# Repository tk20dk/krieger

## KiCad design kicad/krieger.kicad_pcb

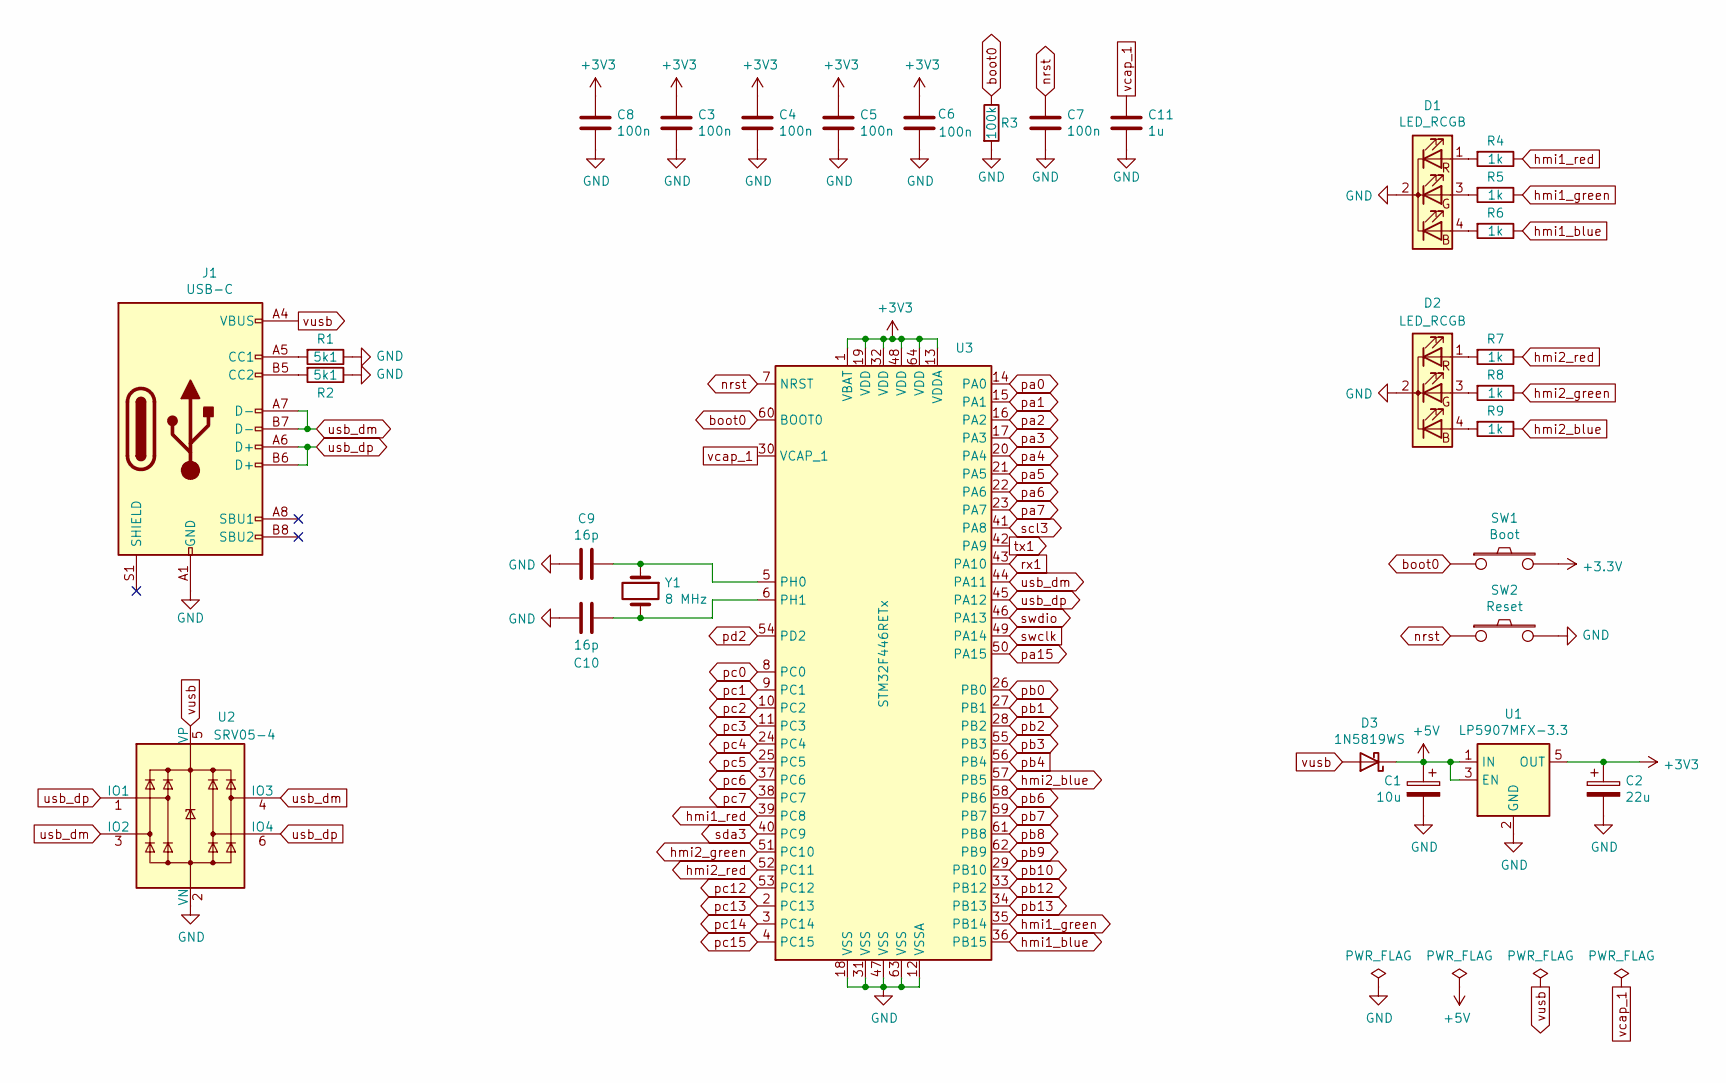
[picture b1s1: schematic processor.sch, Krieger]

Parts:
C1: 10u; CP_EIA-3528-12_Kemet-T
C2: 22u; CP_EIA-3528-12_Kemet-T
C3, C4, C5, C6, C7, C8: 100n; C_0603_1608Metric
C9, C10: 16p; C_0603_1608Metric
C11: 1u; C_0603_1608Metric
D1, D2: LED_RCGB; LED_D5.0mm-4
D3: 1N5819WS; D_SOD-323_HandSoldering
J1: USB-C; USB_C_Receptacle_HRO_TYPE-C-31-M-12
R1, R2: 5k1; R_0603_1608Metric
R3: 100k; R_0603_1608Metric
R4, R5, R6, R7, R8, R9: 1k; R_0603_1608Metric
SW1: Boot; TACT-SWITCH
SW2: Reset; TACT-SWITCH
U1: LP5907MFX-3.3; SOT-23-5
U2: SRV05-4; SOT-23-6
U3: STM32F446RETx; LQFP-64_10x10mm_P0.5mm
Y1: 8 MHz; Crystal_SMD_5032-2Pin_5.0x3.2mm

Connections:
+5V: C1.1, D3.1 (K), U1.1 (IN), U1.3 (EN); also elsewhere on the board
GND: C1.2, C2.2, C3.2, C4.2, C5.2, C6.2, C7.2, C8.2, C9.2, C10.2, C11.2, D1.2 (K), D2.2 (K), J1.A1 (GND), J1.A12 (GND), J1.B1 (GND), J1.B12 (GND), R1.1, R2.1, R3.2, SW2.2, U1.2 (GND), U2.2 (VN), U3.12 (VSSA), U3.18 (VSS), U3.31 (VSS), U3.47 (VSS), U3.63 (VSS); also elsewhere on the board
unnamed: C9.1, U3.5 (PH0), Y1.1
unnamed: C10.1, U3.6 (PH1), Y1.2
unnamed: D1.1 (RA), R4.2
unnamed: D1.3 (GA), R5.2
unnamed: D1.4 (BA), R6.2
unnamed: D2.1 (RA), R7.2
unnamed: D2.3 (GA), R8.2
unnamed: D2.4 (BA), R9.2
unnamed: J1.A5 (CC1), R1.2
unnamed: J1.B5 (CC2), R2.2
boot0: R3.1, SW1.1, U3.60 (BOOT0); also elsewhere on the board
hmi1_blue: R6.1, U3.36 (PB15); also elsewhere on the board
hmi1_green: R5.1, U3.35 (PB14); also elsewhere on the board
hmi1_red: R4.1, U3.39 (PC8); also elsewhere on the board
hmi2_blue: R9.1, U3.57 (PB5); also elsewhere on the board
hmi2_green: R8.1, U3.51 (PC10); also elsewhere on the board
hmi2_red: R7.1, U3.52 (PC11); also elsewhere on the board
nrst: C7.1, SW2.1, U3.7 (NRST); also elsewhere on the board
pa0: U3.14 (PA0); also elsewhere on the board
pa1: U3.15 (PA1); also elsewhere on the board
pa2: U3.16 (PA2); also elsewhere on the board
pa3: U3.17 (PA3); also elsewhere on the board
pa4: U3.20 (PA4); also elsewhere on the board
pa5: U3.21 (PA5); also elsewhere on the board
pa6: U3.22 (PA6); also elsewhere on the board
pa7: U3.23 (PA7); also elsewhere on the board
pa15: U3.50 (PA15); also elsewhere on the board
pb0: U3.26 (PB0); also elsewhere on the board
pb1: U3.27 (PB1); also elsewhere on the board
pb2: U3.28 (PB2); also elsewhere on the board
pb3: U3.55 (PB3); also elsewhere on the board
pb4: U3.56 (PB4); also elsewhere on the board
pb6: U3.58 (PB6); also elsewhere on the board
pb7: U3.59 (PB7); also elsewhere on the board
pb8: U3.61 (PB8); also elsewhere on the board
pb9: U3.62 (PB9); also elsewhere on the board
pb10: U3.29 (PB10); also elsewhere on the board
pb12: U3.33 (PB12); also elsewhere on the board
pb13: U3.34 (PB13); also elsewhere on the board
pc0: U3.8 (PC0); also elsewhere on the board
pc1: U3.9 (PC1); also elsewhere on the board
pc2: U3.10 (PC2); also elsewhere on the board
pc3: U3.11 (PC3); also elsewhere on the board
pc4: U3.24 (PC4); also elsewhere on the board
pc5: U3.25 (PC5); also elsewhere on the board
pc6: U3.37 (PC6); also elsewhere on the board
pc7: U3.38 (PC7); also elsewhere on the board
pc12: U3.53 (PC12); also elsewhere on the board
pc13: U3.2 (PC13); also elsewhere on the board
pc14: U3.3 (PC14); also elsewhere on the board
pc15: U3.4 (PC15); also elsewhere on the board
pd2: U3.54 (PD2); also elsewhere on the board
rx1: U3.43 (PA10); also elsewhere on the board
scl3: U3.41 (PA8); also elsewhere on the board
sda3: U3.40 (PC9); also elsewhere on the board
swclk: U3.49 (PA14); also elsewhere on the board
swdio: U3.46 (PA13); also elsewhere on the board
tx1: U3.42 (PA9); also elsewhere on the board
usb_dm: J1.A7 (D-), J1.B7 (D-), U2.3 (IO2), U2.4 (IO3), U3.44 (PA11)
usb_dp: J1.A6 (D+), J1.B6 (D+), U2.1 (IO1), U2.6 (IO4), U3.45 (PA12)
vcap_1: C11.1, U3.30 (VCAP_1)
vusb: D3.2 (A), J1.A4 (VBUS), J1.A9 (VBUS), J1.B4 (VBUS), J1.B9 (VBUS), U2.5 (VP)

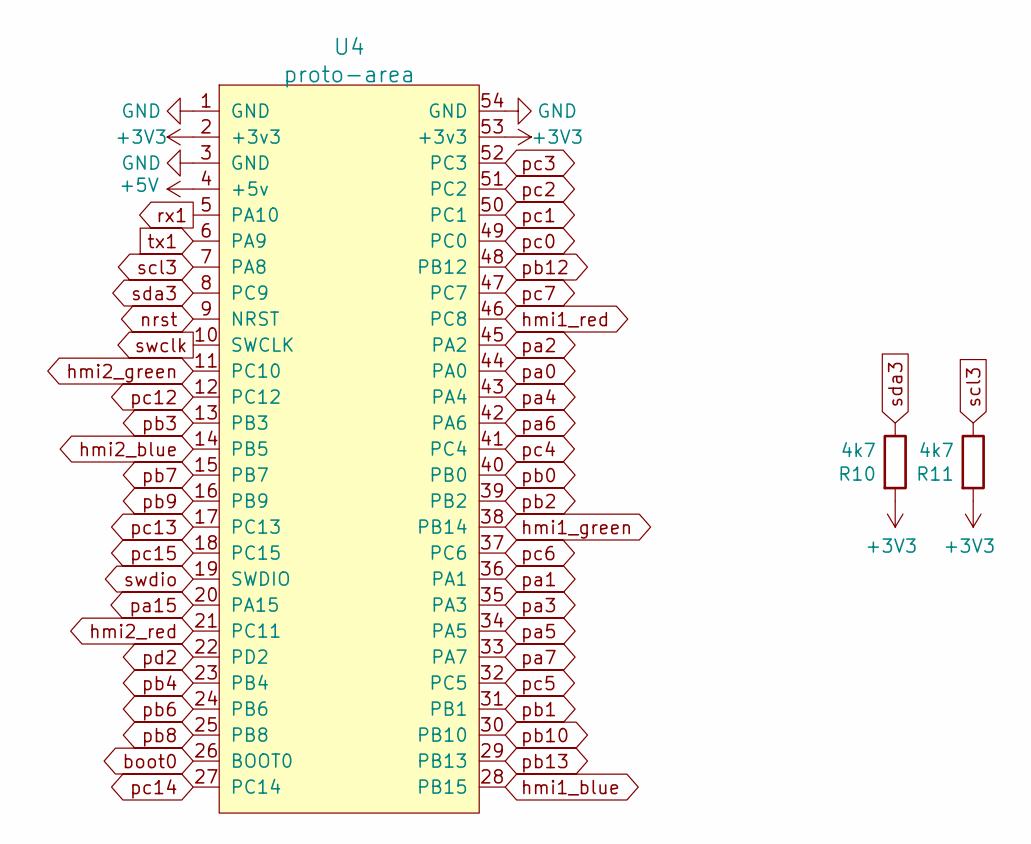
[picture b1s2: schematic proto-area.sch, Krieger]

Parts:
R10, R11: 4k7; R_0603_1608Metric
U4: proto-area

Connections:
+5V: U4.4 (+5v); also elsewhere on the board
GND: U4.1 (GND), U4.3 (GND), U4.54 (GND); also elsewhere on the board
boot0: U4.26 (BOOT0); also elsewhere on the board
hmi1_blue: U4.28 (PB15); also elsewhere on the board
hmi1_green: U4.38 (PB14); also elsewhere on the board
hmi1_red: U4.46 (PC8); also elsewhere on the board
hmi2_blue: U4.14 (PB5); also elsewhere on the board
hmi2_green: U4.11 (PC10); also elsewhere on the board
hmi2_red: U4.21 (PC11); also elsewhere on the board
nrst: U4.9 (NRST); also elsewhere on the board
pa0: U4.44 (PA0); also elsewhere on the board
pa1: U4.36 (PA1); also elsewhere on the board
pa2: U4.45 (PA2); also elsewhere on the board
pa3: U4.35 (PA3); also elsewhere on the board
pa4: U4.43 (PA4); also elsewhere on the board
pa5: U4.34 (PA5); also elsewhere on the board
pa6: U4.42 (PA6); also elsewhere on the board
pa7: U4.33 (PA7); also elsewhere on the board
pa15: U4.20 (PA15); also elsewhere on the board
pb0: U4.40 (PB0); also elsewhere on the board
pb1: U4.31 (PB1); also elsewhere on the board
pb2: U4.39 (PB2); also elsewhere on the board
pb3: U4.13 (PB3); also elsewhere on the board
pb4: U4.23 (PB4); also elsewhere on the board
pb6: U4.24 (PB6); also elsewhere on the board
pb7: U4.15 (PB7); also elsewhere on the board
pb8: U4.25 (PB8); also elsewhere on the board
pb9: U4.16 (PB9); also elsewhere on the board
pb10: U4.30 (PB10); also elsewhere on the board
pb12: U4.48 (PB12); also elsewhere on the board
pb13: U4.29 (PB13); also elsewhere on the board
pc0: U4.49 (PC0); also elsewhere on the board
pc1: U4.50 (PC1); also elsewhere on the board
pc2: U4.51 (PC2); also elsewhere on the board
pc3: U4.52 (PC3); also elsewhere on the board
pc4: U4.41 (PC4); also elsewhere on the board
pc5: U4.32 (PC5); also elsewhere on the board
pc6: U4.37 (PC6); also elsewhere on the board
pc7: U4.47 (PC7); also elsewhere on the board
pc12: U4.12 (PC12); also elsewhere on the board
pc13: U4.17 (PC13); also elsewhere on the board
pc14: U4.27 (PC14); also elsewhere on the board
pc15: U4.18 (PC15); also elsewhere on the board
pd2: U4.22 (PD2); also elsewhere on the board
rx1: U4.5 (PA10); also elsewhere on the board
scl3: R11.1, U4.7 (PA8); also elsewhere on the board
sda3: R10.1, U4.8 (PC9); also elsewhere on the board
swclk: U4.10 (SWCLK); also elsewhere on the board
swdio: U4.19 (SWDIO); also elsewhere on the board
tx1: U4.6 (PA9); also elsewhere on the board

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
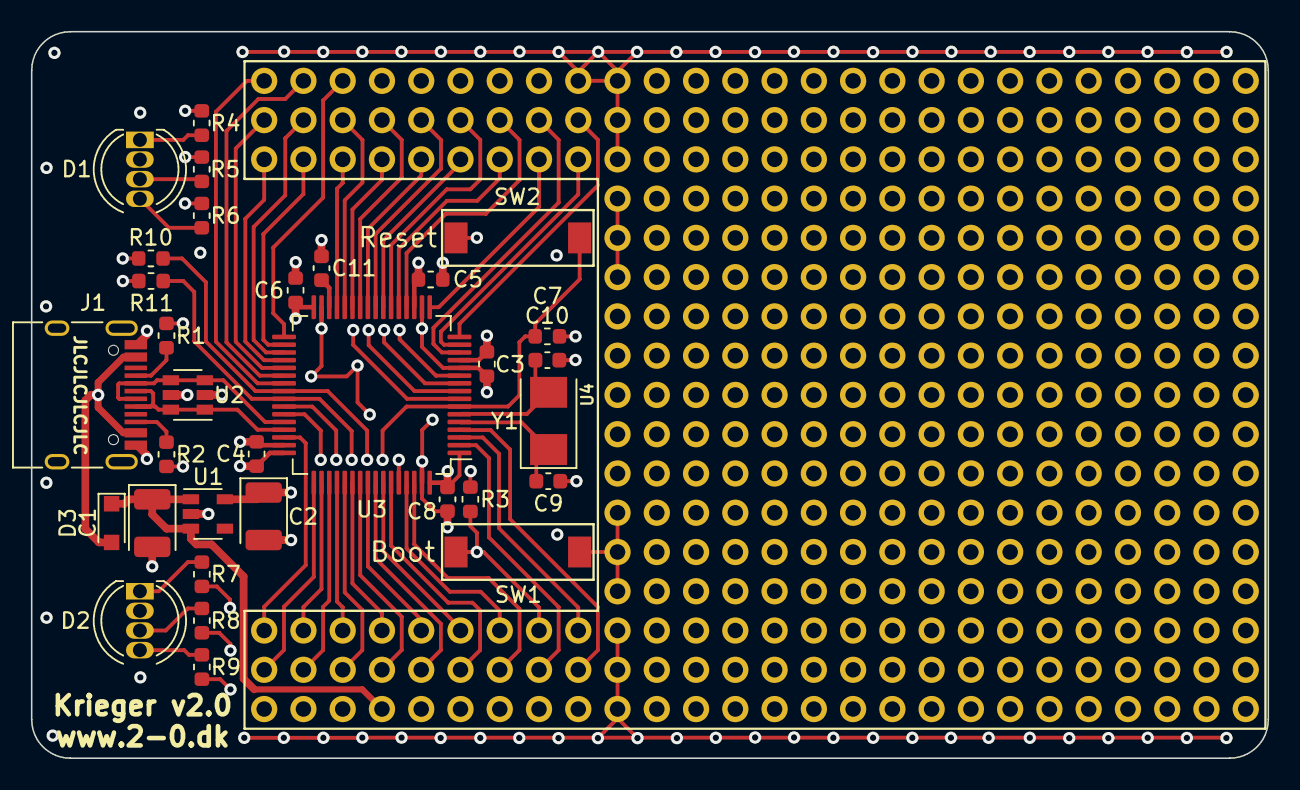
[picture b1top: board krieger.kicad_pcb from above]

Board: 4 copper layers, 80.0 x 47.0 mm, 33 parts (0 on the bottom side), 65 nets.

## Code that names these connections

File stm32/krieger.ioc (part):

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Mcu.Name=STM32F446R(C-E)Tx
Mcu.Package=LQFP64
Mcu.UserName=STM32F446RETx
PA11.Mode=Device_Only
PA11.Signal=USB_OTG_FS_DM
PA12.Mode=Device_Only
PA12.Signal=USB_OTG_FS_DP
PA13.Mode=Serial_Wire
PA13.Signal=SYS_JTMS-SWDIO
PA14.Mode=Serial_Wire
PA14.Signal=SYS_JTCK-SWCLK
PB14.GPIOParameters=GPIO_Label
PB14.GPIO_Label=HMI_LED1_GREEN
PB14.Signal=GPIO_Output
PB15.GPIOParameters=GPIO_Label
PB15.GPIO_Label=HMI_LED1_BLUE
PB15.Signal=GPIO_Output
PB5.GPIOParameters=GPIO_Label
PB5.GPIO_Label=HMI_LED2_BLUE
PB5.Signal=GPIO_Output
PC10.GPIOParameters=GPIO_Label
PC10.GPIO_Label=HMI_LED2_GREEN
PC10.Signal=GPIO_Output
PC11.GPIOParameters=GPIO_Label
PC11.GPIO_Label=HMI_LED2_RED
PC11.Signal=GPIO_Output
PC8.GPIOParameters=GPIO_Label
PC8.GPIO_Label=HMI_LED1_RED
PC8.Signal=GPIO_Output
PH0-OSC_IN.Mode=HSE-External-Oscillator
PH0-OSC_IN.Signal=RCC_OSC_IN
PH1-OSC_OUT.Mode=HSE-External-Oscillator
PH1-OSC_OUT.Signal=RCC_OSC_OUT
RCC.HSE_VALUE=8000000
RCC.SYSCLKFreq_VALUE=180000000
RCC.SYSCLKSource=RCC_SYSCLKSOURCE_PLLCLK
board=custom

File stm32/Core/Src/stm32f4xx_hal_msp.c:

/* USER CODE BEGIN Header */
/**
  ******************************************************************************
  * @file         stm32f4xx_hal_msp.c
  * @brief        This file provides code for the MSP Initialization
  *               and de-Initialization codes.
  ******************************************************************************
  * @attention
  *
  * <h2><center>&copy; Copyright (c) 2021 STMicroelectronics.
  * All rights reserved.</center></h2>
  *
  * This software component is licensed by ST under BSD 3-Clause license,
  * the "License"; You may not use this file except in compliance with the
  * License. You may obtain a copy of the License at:
  *                        opensource.org/licenses/BSD-3-Clause
  *
  ******************************************************************************
  */
/* USER CODE END Header */

/* Includes ------------------------------------------------------------------*/
#include "main.h"
/* USER CODE BEGIN Includes */

/* USER CODE END Includes */

/* Private typedef -----------------------------------------------------------*/
/* USER CODE BEGIN TD */

/* USER CODE END TD */

/* Private define ------------------------------------------------------------*/
/* USER CODE BEGIN Define */

/* USER CODE END Define */

/* Private macro -------------------------------------------------------------*/
/* USER CODE BEGIN Macro */

/* USER CODE END Macro */

/* Private variables ---------------------------------------------------------*/
/* USER CODE BEGIN PV */

/* USER CODE END PV */

/* Private function prototypes -----------------------------------------------*/
/* USER CODE BEGIN PFP */

/* USER CODE END PFP */

/* External functions --------------------------------------------------------*/
/* USER CODE BEGIN ExternalFunctions */

/* USER CODE END ExternalFunctions */

/* USER CODE BEGIN 0 */

/* USER CODE END 0 */
/**
  * Initializes the Global MSP.
  */
void HAL_MspInit(void)
{
  /* USER CODE BEGIN MspInit 0 */

  /* USER CODE END MspInit 0 */

  __HAL_RCC_SYSCFG_CLK_ENABLE();
  __HAL_RCC_PWR_CLK_ENABLE();

  /* System interrupt init*/

  /* USER CODE BEGIN MspInit 1 */

  /* USER CODE END MspInit 1 */
}

/**
* @brief I2C MSP Initialization
* This function configures the hardware resources used in this example
* @param hi2c: I2C handle pointer
* @retval None
*/
void HAL_I2C_MspInit(I2C_HandleTypeDef* hi2c)
{
  GPIO_InitTypeDef GPIO_InitStruct = {0};
  if(hi2c->Instance==I2C3)
  {
  /* USER CODE BEGIN I2C3_MspInit 0 */

  /* USER CODE END I2C3_MspInit 0 */

    __HAL_RCC_GPIOC_CLK_ENABLE();
    __HAL_RCC_GPIOA_CLK_ENABLE();
    /**I2C3 GPIO Configuration
    PC9     ------> I2C3_SDA
    PA8     ------> I2C3_SCL
    */
    GPIO_InitStruct.Pin = GPIO_PIN_9;
    GPIO_InitStruct.Mode = GPIO_MODE_AF_OD;
    GPIO_InitStruct.Pull = GPIO_PULLUP;
    GPIO_InitStruct.Speed = GPIO_SPEED_FREQ_VERY_HIGH;
    GPIO_InitStruct.Alternate = GPIO_AF4_I2C3;
    HAL_GPIO_Init(GPIOC, &GPIO_InitStruct);

    GPIO_InitStruct.Pin = GPIO_PIN_8;
    GPIO_InitStruct.Mode = GPIO_MODE_AF_OD;
    GPIO_InitStruct.Pull = GPIO_PULLUP;
    GPIO_InitStruct.Speed = GPIO_SPEED_FREQ_VERY_HIGH;
    GPIO_InitStruct.Alternate = GPIO_AF4_I2C3;
    HAL_GPIO_Init(GPIOA, &GPIO_InitStruct);

    /* Peripheral clock enable */
    __HAL_RCC_I2C3_CLK_ENABLE();
  /* USER CODE BEGIN I2C3_MspInit 1 */

  /* USER CODE END I2C3_MspInit 1 */
  }

}

/**
* @brief I2C MSP De-Initialization
* This function freeze the hardware resources used in this example
* @param hi2c: I2C handle pointer
* @retval None
*/
void HAL_I2C_MspDeInit(I2C_HandleTypeDef* hi2c)
{
  if(hi2c->Instance==I2C3)
  {
  /* USER CODE BEGIN I2C3_MspDeInit 0 */

  /* USER CODE END I2C3_MspDeInit 0 */
    /* Peripheral clock disable */
    __HAL_RCC_I2C3_CLK_DISABLE();

    /**I2C3 GPIO Configuration
    PC9     ------> I2C3_SDA
    PA8     ------> I2C3_SCL
    */
    HAL_GPIO_DeInit(GPIOC, GPIO_PIN_9);

    HAL_GPIO_DeInit(GPIOA, GPIO_PIN_8);

  /* USER CODE BEGIN I2C3_MspDeInit 1 */

  /* USER CODE END I2C3_MspDeInit 1 */
  }

}

/**
* @brief UART MSP Initialization
* This function configures the hardware resources used in this example
* @param huart: UART handle pointer
* @retval None
*/
void HAL_UART_MspInit(UART_HandleTypeDef* huart)
{
  GPIO_InitTypeDef GPIO_InitStruct = {0};
  if(huart->Instance==USART1)
  {
  /* USER CODE BEGIN USART1_MspInit 0 */

  /* USER CODE END USART1_MspInit 0 */
    /* Peripheral clock enable */
    __HAL_RCC_USART1_CLK_ENABLE();

    __HAL_RCC_GPIOA_CLK_ENABLE();
    /**USART1 GPIO Configuration
    PA9     ------> USART1_TX
    PA10     ------> USART1_RX
    */
    GPIO_InitStruct.Pin = GPIO_PIN_9|GPIO_PIN_10;
    GPIO_InitStruct.Mode = GPIO_MODE_AF_PP;
    GPIO_InitStruct.Pull = GPIO_NOPULL;
    GPIO_InitStruct.Speed = GPIO_SPEED_FREQ_VERY_HIGH;
    GPIO_InitStruct.Alternate = GPIO_AF7_USART1;
    HAL_GPIO_Init(GPIOA, &GPIO_InitStruct);

  /* USER CODE BEGIN USART1_MspInit 1 */

  /* USER CODE END USART1_MspInit 1 */
  }

}

/**
* @brief UART MSP De-Initialization
* This function freeze the hardware resources used in this example
* @param huart: UART handle pointer
* @retval None
*/
void HAL_UART_MspDeInit(UART_HandleTypeDef* huart)
{
  if(huart->Instance==USART1)
  {
  /* USER CODE BEGIN USART1_MspDeInit 0 */

  /* USER CODE END USART1_MspDeInit 0 */
    /* Peripheral clock disable */
    __HAL_RCC_USART1_CLK_DISABLE();

    /**USART1 GPIO Configuration
    PA9     ------> USART1_TX
    PA10     ------> USART1_RX
    */
    HAL_GPIO_DeInit(GPIOA, GPIO_PIN_9|GPIO_PIN_10);

  /* USER CODE BEGIN USART1_MspDeInit 1 */

  /* USER CODE END USART1_MspDeInit 1 */
  }

}

/**
* @brief PCD MSP Initialization
* This function configures the hardware resources used in this example
* @param hpcd: PCD handle pointer
* @retval None
*/
void HAL_PCD_MspInit(PCD_HandleTypeDef* hpcd)
{
  GPIO_InitTypeDef GPIO_InitStruct = {0};
  if(hpcd->Instance==USB_OTG_FS)
  {
  /* USER CODE BEGIN USB_OTG_FS_MspInit 0 */

  /* USER CODE END USB_OTG_FS_MspInit 0 */

    __HAL_RCC_GPIOA_CLK_ENABLE();
    /**USB_OTG_FS GPIO Configuration
    PA11     ------> USB_OTG_FS_DM
    PA12     ------> USB_OTG_FS_DP
    */
    GPIO_InitStruct.Pin = GPIO_PIN_11|GPIO_PIN_12;
    GPIO_InitStruct.Mode = GPIO_MODE_AF_PP;
    GPIO_InitStruct.Pull = GPIO_NOPULL;
    GPIO_InitStruct.Speed = GPIO_SPEED_FREQ_VERY_HIGH;
    GPIO_InitStruct.Alternate = GPIO_AF10_OTG_FS;
    HAL_GPIO_Init(GPIOA, &GPIO_InitStruct);

    /* Peripheral clock enable */
    __HAL_RCC_USB_OTG_FS_CLK_ENABLE();
  /* USER CODE BEGIN USB_OTG_FS_MspInit 1 */

  /* USER CODE END USB_OTG_FS_MspInit 1 */
  }

}

/**
* @brief PCD MSP De-Initialization
* This function freeze the hardware resources used in this example
* @param hpcd: PCD handle pointer
* @retval None
*/
void HAL_PCD_MspDeInit(PCD_HandleTypeDef* hpcd)
{
  if(hpcd->Instance==USB_OTG_FS)
  {
  /* USER CODE BEGIN USB_OTG_FS_MspDeInit 0 */

  /* USER CODE END USB_OTG_FS_MspDeInit 0 */
    /* Peripheral clock disable */
    __HAL_RCC_USB_OTG_FS_CLK_DISABLE();

    /**USB_OTG_FS GPIO Configuration
    PA11     ------> USB_OTG_FS_DM
    PA12     ------> USB_OTG_FS_DP
    */
    HAL_GPIO_DeInit(GPIOA, GPIO_PIN_11|GPIO_PIN_12);

  /* USER CODE BEGIN USB_OTG_FS_MspDeInit 1 */

  /* USER CODE END USB_OTG_FS_MspDeInit 1 */
  }

}

/* USER CODE BEGIN 1 */

/* USER CODE END 1 */

/************************ (C) COPYRIGHT STMicroelectronics *****END OF FILE****/

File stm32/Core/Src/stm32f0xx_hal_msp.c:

/* USER CODE BEGIN Header */
/**
  ******************************************************************************
  * File Name          : stm32f0xx_hal_msp.c
  * Description        : This file provides code for the MSP Initialization
  *                      and de-Initialization codes.
  ******************************************************************************
  * @attention
  *
  * <h2><center>&copy; Copyright (c) 2020 STMicroelectronics.
  * All rights reserved.</center></h2>
  *
  * This software component is licensed by ST under BSD 3-Clause license,
  * the "License"; You may not use this file except in compliance with the
  * License. You may obtain a copy of the License at:
  *                        opensource.org/licenses/BSD-3-Clause
  *
  ******************************************************************************
  */
/* USER CODE END Header */

/* Includes ------------------------------------------------------------------*/
#include "main.h"
/* USER CODE BEGIN Includes */

/* USER CODE END Includes */

/* Private typedef -----------------------------------------------------------*/
/* USER CODE BEGIN TD */

/* USER CODE END TD */

/* Private define ------------------------------------------------------------*/
/* USER CODE BEGIN Define */

/* USER CODE END Define */

/* Private macro -------------------------------------------------------------*/
/* USER CODE BEGIN Macro */

/* USER CODE END Macro */

/* Private variables ---------------------------------------------------------*/
/* USER CODE BEGIN PV */

/* USER CODE END PV */

/* Private function prototypes -----------------------------------------------*/
/* USER CODE BEGIN PFP */

/* USER CODE END PFP */

/* External functions --------------------------------------------------------*/
/* USER CODE BEGIN ExternalFunctions */

/* USER CODE END ExternalFunctions */

/* USER CODE BEGIN 0 */

/* USER CODE END 0 */
/**
  * Initializes the Global MSP.
  */
void HAL_MspInit(void)
{
  /* USER CODE BEGIN MspInit 0 */

  /* USER CODE END MspInit 0 */

  __HAL_RCC_SYSCFG_CLK_ENABLE();
  __HAL_RCC_PWR_CLK_ENABLE();

  /* System interrupt init*/

  /* USER CODE BEGIN MspInit 1 */

  /* USER CODE END MspInit 1 */
}

/**
* @brief I2C MSP Initialization
* This function configures the hardware resources used in this example
* @param hi2c: I2C handle pointer
* @retval None
*/
void HAL_I2C_MspInit(I2C_HandleTypeDef* hi2c)
{
  GPIO_InitTypeDef GPIO_InitStruct = {0};
  if(hi2c->Instance==I2C2)
  {
  /* USER CODE BEGIN I2C2_MspInit 0 */

  /* USER CODE END I2C2_MspInit 0 */

    __HAL_RCC_GPIOB_CLK_ENABLE();
    /**I2C2 GPIO Configuration
    PB10     ------> I2C2_SCL
    PB11     ------> I2C2_SDA
    */
    GPIO_InitStruct.Pin = GPIO_PIN_10|GPIO_PIN_11;
    GPIO_InitStruct.Mode = GPIO_MODE_AF_OD;
    GPIO_InitStruct.Pull = GPIO_PULLUP;
    GPIO_InitStruct.Speed = GPIO_SPEED_FREQ_HIGH;
    GPIO_InitStruct.Alternate = GPIO_AF1_I2C2;
    HAL_GPIO_Init(GPIOB, &GPIO_InitStruct);

    /* Peripheral clock enable */
    __HAL_RCC_I2C2_CLK_ENABLE();
  /* USER CODE BEGIN I2C2_MspInit 1 */

  /* USER CODE END I2C2_MspInit 1 */
  }

}

/**
* @brief I2C MSP De-Initialization
* This function freeze the hardware resources used in this example
* @param hi2c: I2C handle pointer
* @retval None
*/
void HAL_I2C_MspDeInit(I2C_HandleTypeDef* hi2c)
{
  if(hi2c->Instance==I2C2)
  {
  /* USER CODE BEGIN I2C2_MspDeInit 0 */

  /* USER CODE END I2C2_MspDeInit 0 */
    /* Peripheral clock disable */
    __HAL_RCC_I2C2_CLK_DISABLE();

    /**I2C2 GPIO Configuration
    PB10     ------> I2C2_SCL
    PB11     ------> I2C2_SDA
    */
    HAL_GPIO_DeInit(GPIOB, GPIO_PIN_10);

    HAL_GPIO_DeInit(GPIOB, GPIO_PIN_11);

  /* USER CODE BEGIN I2C2_MspDeInit 1 */

  /* USER CODE END I2C2_MspDeInit 1 */
  }

}

/**
* @brief SPI MSP Initialization
* This function configures the hardware resources used in this example
* @param hspi: SPI handle pointer
* @retval None
*/
void HAL_SPI_MspInit(SPI_HandleTypeDef* hspi)
{
  GPIO_InitTypeDef GPIO_InitStruct = {0};
  if(hspi->Instance==SPI1)
  {
  /* USER CODE BEGIN SPI1_MspInit 0 */

  /* USER CODE END SPI1_MspInit 0 */
    /* Peripheral clock enable */
    __HAL_RCC_SPI1_CLK_ENABLE();

    __HAL_RCC_GPIOA_CLK_ENABLE();
    /**SPI1 GPIO Configuration
    PA5     ------> SPI1_SCK
    PA6     ------> SPI1_MISO
    PA7     ------> SPI1_MOSI
    */
    GPIO_InitStruct.Pin = GPIO_PIN_5|GPIO_PIN_6|GPIO_PIN_7;
    GPIO_InitStruct.Mode = GPIO_MODE_AF_PP;
    GPIO_InitStruct.Pull = GPIO_NOPULL;
    GPIO_InitStruct.Speed = GPIO_SPEED_FREQ_HIGH;
    GPIO_InitStruct.Alternate = GPIO_AF0_SPI1;
    HAL_GPIO_Init(GPIOA, &GPIO_InitStruct);

  /* USER CODE BEGIN SPI1_MspInit 1 */

  /* USER CODE END SPI1_MspInit 1 */
  }

}

/**
* @brief SPI MSP De-Initialization
* This function freeze the hardware resources used in this example
* @param hspi: SPI handle pointer
* @retval None
*/
void HAL_SPI_MspDeInit(SPI_HandleTypeDef* hspi)
{
  if(hspi->Instance==SPI1)
  {
  /* USER CODE BEGIN SPI1_MspDeInit 0 */

  /* USER CODE END SPI1_MspDeInit 0 */
    /* Peripheral clock disable */
    __HAL_RCC_SPI1_CLK_DISABLE();

    /**SPI1 GPIO Configuration
    PA5     ------> SPI1_SCK
    PA6     ------> SPI1_MISO
    PA7     ------> SPI1_MOSI
    */
    HAL_GPIO_DeInit(GPIOA, GPIO_PIN_5|GPIO_PIN_6|GPIO_PIN_7);

  /* USER CODE BEGIN SPI1_MspDeInit 1 */

  /* USER CODE END SPI1_MspDeInit 1 */
  }

}

/**
* @brief UART MSP Initialization
* This function configures the hardware resources used in this example
* @param huart: UART handle pointer
* @retval None
*/
void HAL_UART_MspInit(UART_HandleTypeDef* huart)
{
  GPIO_InitTypeDef GPIO_InitStruct = {0};
  if(huart->Instance==USART2)
  {
  /* USER CODE BEGIN USART2_MspInit 0 */

  /* USER CODE END USART2_MspInit 0 */
    /* Peripheral clock enable */
    __HAL_RCC_USART2_CLK_ENABLE();

    __HAL_RCC_GPIOA_CLK_ENABLE();
    /**USART2 GPIO Configuration
    PA2     ------> USART2_TX
    PA3     ------> USART2_RX
    */
    GPIO_InitStruct.Pin = GPIO_PIN_2|GPIO_PIN_3;
    GPIO_InitStruct.Mode = GPIO_MODE_AF_PP;
    GPIO_InitStruct.Pull = GPIO_NOPULL;
    GPIO_InitStruct.Speed = GPIO_SPEED_FREQ_HIGH;
    GPIO_InitStruct.Alternate = GPIO_AF1_USART2;
    HAL_GPIO_Init(GPIOA, &GPIO_InitStruct);

  /* USER CODE BEGIN USART2_MspInit 1 */

  /* USER CODE END USART2_MspInit 1 */
  }

}

/**
* @brief UART MSP De-Initialization
* This function freeze the hardware resources used in this example
* @param huart: UART handle pointer
* @retval None
*/
void HAL_UART_MspDeInit(UART_HandleTypeDef* huart)
{
  if(huart->Instance==USART2)
  {
  /* USER CODE BEGIN USART2_MspDeInit 0 */

  /* USER CODE END USART2_MspDeInit 0 */
    /* Peripheral clock disable */
    __HAL_RCC_USART2_CLK_DISABLE();

    /**USART2 GPIO Configuration
    PA2     ------> USART2_TX
    PA3     ------> USART2_RX
    */
    HAL_GPIO_DeInit(GPIOA, GPIO_PIN_2|GPIO_PIN_3);

  /* USER CODE BEGIN USART2_MspDeInit 1 */

  /* USER CODE END USART2_MspDeInit 1 */
  }

}

/**
* @brief PCD MSP Initialization
* This function configures the hardware resources used in this example
* @param hpcd: PCD handle pointer
* @retval None
*/
void HAL_PCD_MspInit(PCD_HandleTypeDef* hpcd)
{
  if(hpcd->Instance==USB)
  {
  /* USER CODE BEGIN USB_MspInit 0 */

  /* USER CODE END USB_MspInit 0 */
    /* Peripheral clock enable */
    __HAL_RCC_USB_CLK_ENABLE();
  /* USER CODE BEGIN USB_MspInit 1 */

  /* USER CODE END USB_MspInit 1 */
  }

}

/**
* @brief PCD MSP De-Initialization
* This function freeze the hardware resources used in this example
* @param hpcd: PCD handle pointer
* @retval None
*/
void HAL_PCD_MspDeInit(PCD_HandleTypeDef* hpcd)
{
  if(hpcd->Instance==USB)
  {
  /* USER CODE BEGIN USB_MspDeInit 0 */

  /* USER CODE END USB_MspDeInit 0 */
    /* Peripheral clock disable */
    __HAL_RCC_USB_CLK_DISABLE();
  /* USER CODE BEGIN USB_MspDeInit 1 */

  /* USER CODE END USB_MspDeInit 1 */
  }

}

/* USER CODE BEGIN 1 */

/* USER CODE END 1 */

/************************ (C) COPYRIGHT STMicroelectronics *****END OF FILE****/

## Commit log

2021-05-24 Krieger_v2.00
2021-06-05 Krieger v2.00
2021-06-26 stm32 - led and usb is woring
